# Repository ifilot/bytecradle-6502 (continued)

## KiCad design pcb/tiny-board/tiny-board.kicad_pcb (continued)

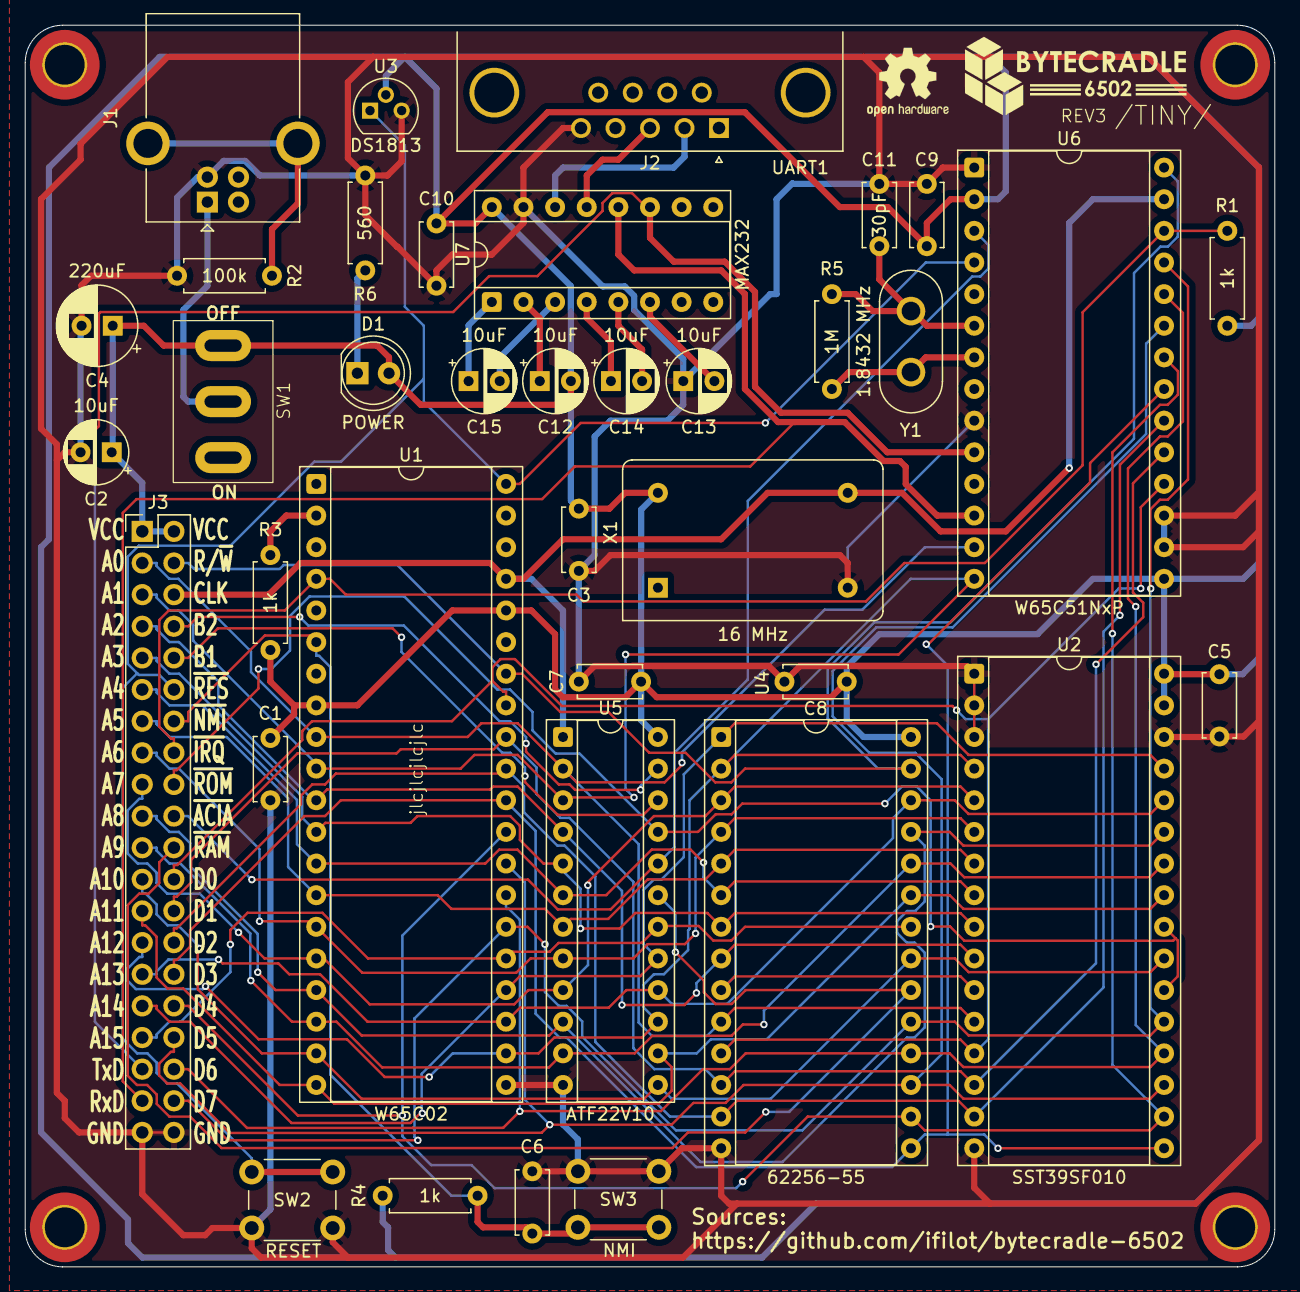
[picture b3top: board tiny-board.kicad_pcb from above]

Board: 2 copper layers, 100.3 x 99.7 mm, 42 parts (0 on the bottom side), 52 nets.

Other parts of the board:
G002: OSHW-Logo2_7.3x6mm_SilkScreen

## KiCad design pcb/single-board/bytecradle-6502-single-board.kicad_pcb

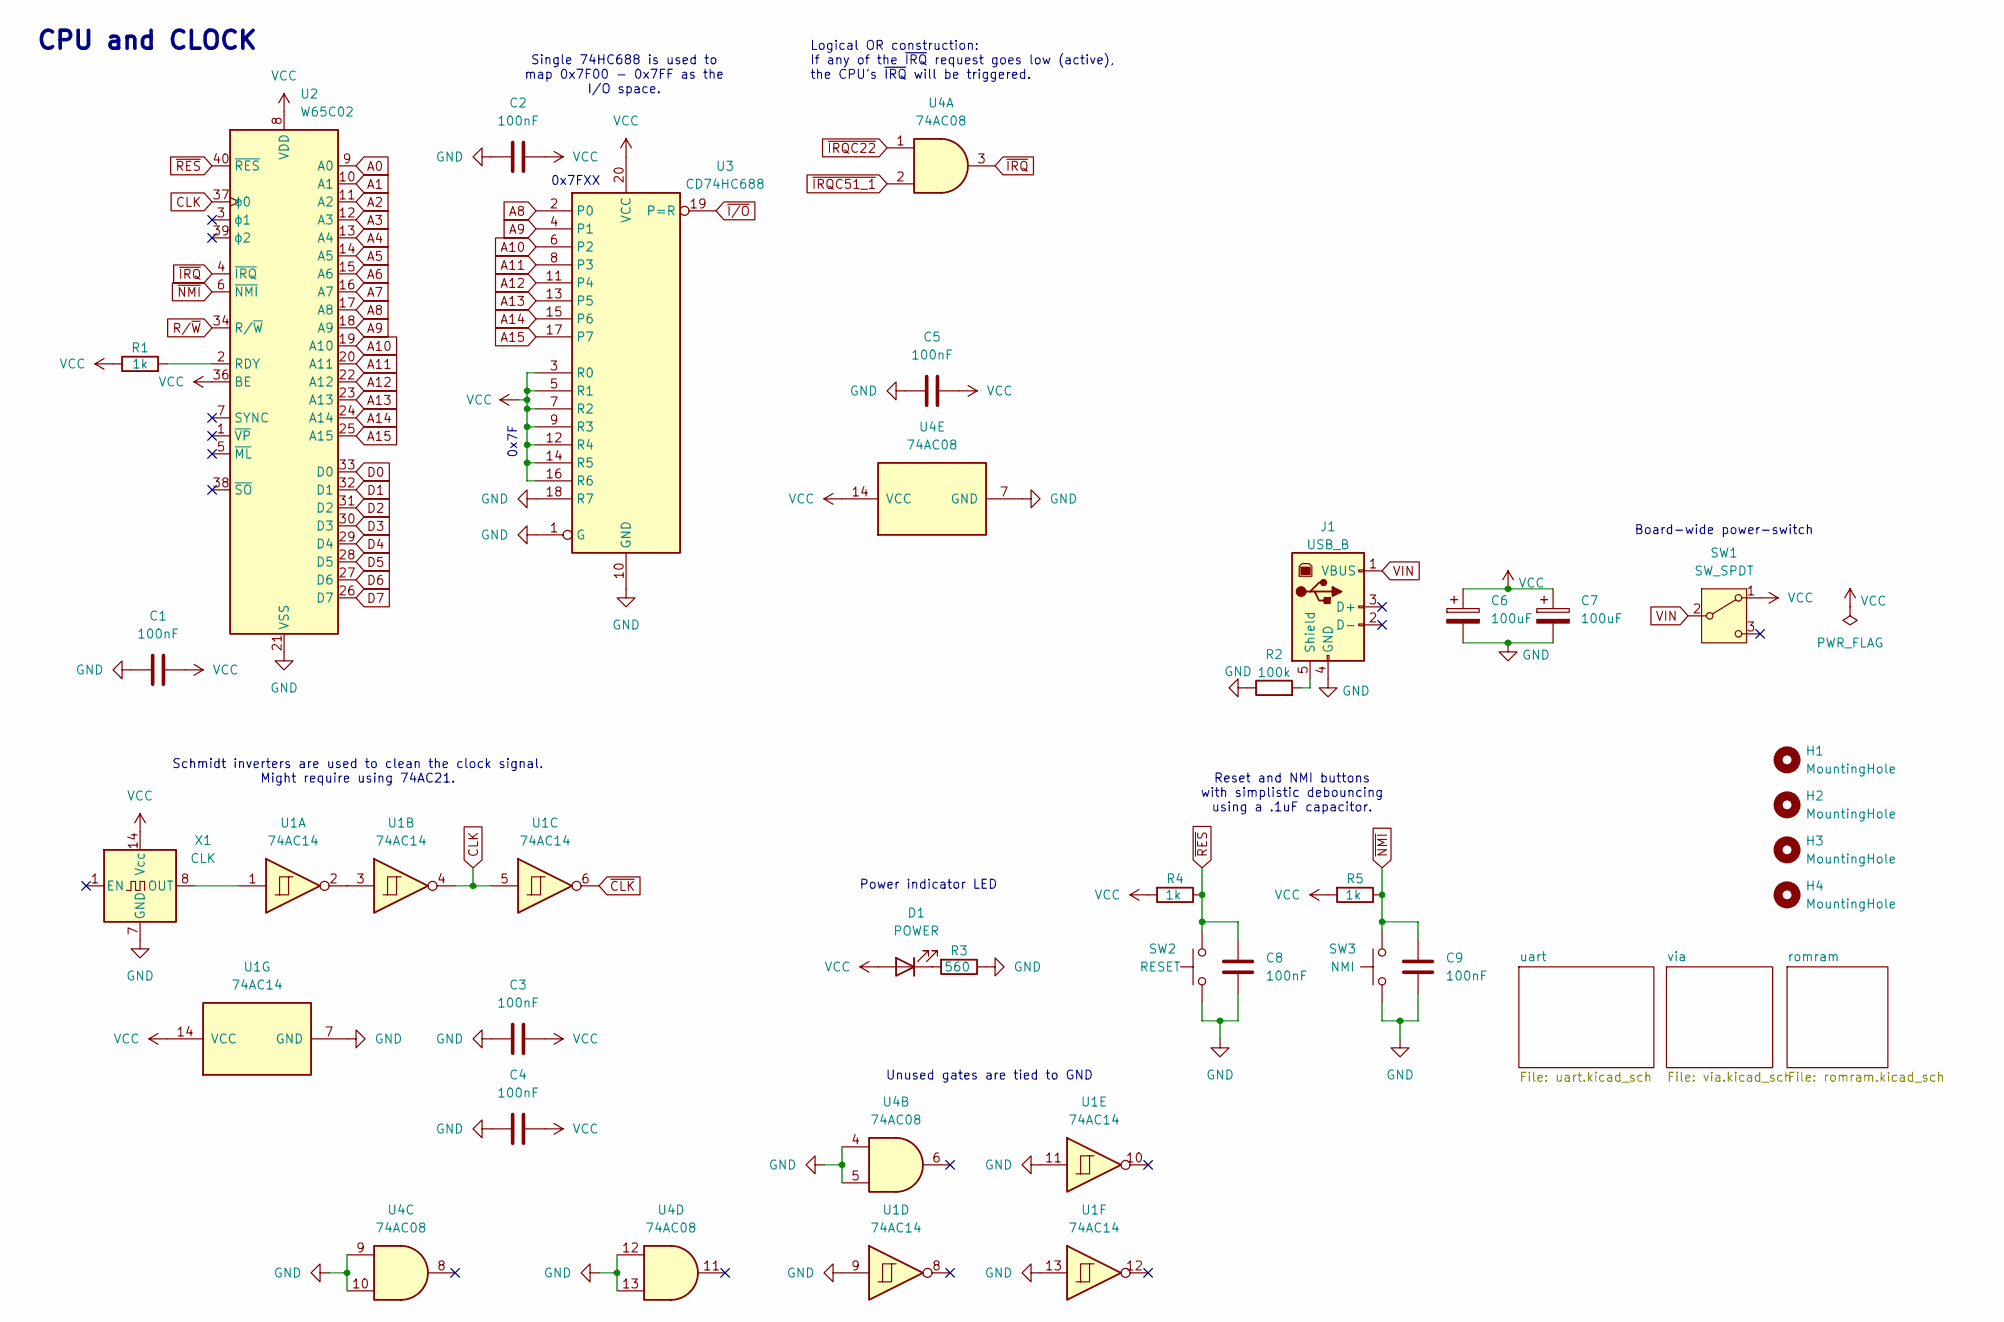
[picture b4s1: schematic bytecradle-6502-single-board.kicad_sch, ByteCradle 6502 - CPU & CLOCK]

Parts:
C1, C2, C3, C4, C5, C8, C9: 100nF; C_Disc_D5.0mm_W2.5mm_P5.00mm
C6, C7: 100uF; CP_Radial_D6.3mm_P2.50mm
D1: POWER; LED_D5.0mm
H1, H2, H3, H4: MountingHole; MountingHole_3.2mm_M3_DIN965_Pad_TopOnly
J1: USB_B; USB_B_OST_USB-B1HSxx_Horizontal
R1, R4, R5: 1k; R_Axial_DIN0207_L6.3mm_D2.5mm_P7.62mm_Horizontal
R2: 100k; R_Axial_DIN0207_L6.3mm_D2.5mm_P7.62mm_Horizontal
R3: 560; R_Axial_DIN0207_L6.3mm_D2.5mm_P7.62mm_Horizontal
SW1: SW_SPDT; power_switch
SW2: RESET; SW_PUSH_6mm
SW3: NMI; SW_PUSH_6mm
U1: 74AC14; DIP-14_W7.62mm_Socket
U2: W65C02; DIP-40_W15.24mm_Socket
U3: CD74HC688; DIP-20_W7.62mm_Socket
U4: 74AC08; DIP-14_W7.62mm_Socket
X1: CLK; Oscillator_DIP-14

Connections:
A0: U2.9 (A0); also elsewhere on the board
A1: U2.10 (A1); also elsewhere on the board
A2: U2.11 (A2); also elsewhere on the board
A3: U2.12 (A3); also elsewhere on the board
A4: U2.13 (A4); also elsewhere on the board
A5: U2.14 (A5); also elsewhere on the board
A6: U2.15 (A6); also elsewhere on the board
A7: U2.16 (A7); also elsewhere on the board
A8: U2.17 (A8), U3.2 (P0); also elsewhere on the board
A9: U2.18 (A9), U3.4 (P1); also elsewhere on the board
A10: U2.19 (A10), U3.6 (P2); also elsewhere on the board
A11: U2.20 (A11), U3.8 (P3); also elsewhere on the board
A12: U2.22 (A12), U3.11 (P4); also elsewhere on the board
A13: U2.23 (A13), U3.13 (P5); also elsewhere on the board
A14: U2.24 (A14), U3.15 (P6); also elsewhere on the board
A15: U2.25 (A15), U3.17 (P7); also elsewhere on the board
CLK: U1.4, U1.5, U2.37 (ϕ0); also elsewhere on the board
D0: U2.33 (D0); also elsewhere on the board
D1: U2.32 (D1); also elsewhere on the board
D2: U2.31 (D2); also elsewhere on the board
D3: U2.30 (D3); also elsewhere on the board
D4: U2.29 (D4); also elsewhere on the board
D5: U2.28 (D5); also elsewhere on the board
D6: U2.27 (D6); also elsewhere on the board
D7: U2.26 (D7); also elsewhere on the board
GND: C1.2, C2.2, C3.2, C4.2, C5.2, C6.2, C7.2, C8.2, C9.2, J1.4 (GND), R2.1, R3.1, SW2.1, SW3.1, U1.7 (GND), U1.9, U1.11, U1.13, U2.21 (VSS), U3.1 (G), U3.10 (GND), U3.18 (R7), U4.4, U4.5, U4.7 (GND), U4.9, U4.10, U4.12, U4.13, X1.7 (GND); also elsewhere on the board
unnamed: D1.1 (K), R3.2
unnamed: J1.5 (Shield), R2.2
unnamed: U1.2, U1.3
unnamed: R1.2, U2.2 (RDY)
unnamed: U1.1, X1.8 (OUT)
R/~W: U2.34 (R/~W); also elsewhere on the board
VCC: C1.1, C2.1, C3.1, C4.1, C5.1, C6.1, C7.1, D1.2 (A), R1.1, R4.2, R5.2, SW1.1 (A), U1.14 (VCC), U2.8 (VDD), U2.36 (BE), U3.3 (R0), U3.5 (R1), U3.7 (R2), U3.9 (R3), U3.12 (R4), U3.14 (R5), U3.16 (R6), U3.20 (VCC), U4.14 (VCC), X1.14 (Vcc); also elsewhere on the board
VIN: J1.1 (VBUS), SW1.2 (B)
~CLK: U1.6
~IRQC22: U4.1; also elsewhere on the board
~IRQC51_1: U4.2; also elsewhere on the board
~IRQ: U2.4 (~IRQ), U4.3
~I/O: U3.19 (P=R); also elsewhere on the board
~NMI: C9.1, R5.1, SW3.2, U2.6 (~NMI); also elsewhere on the board
~RES: C8.1, R4.1, SW2.2, U2.40 (~RES); also elsewhere on the board

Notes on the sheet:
0x7F
Reset and NMI buttons with simplistic debouncing using a .1uF capacitor.
Schmidt inverters are used to clean the clock signal. Might require using 74AC21.
0x7FXX
Power indicator LED
Single 74HC688 is used to map 0x7F00 - 0x7FF as the I/O space.
CPU and CLOCK
Board-wide power-switch
Logical OR construction: If any of the ~{IRQ} request goes low (active), the CPU's ~{IRQ} will be triggered.
Unused gates are tied to GND

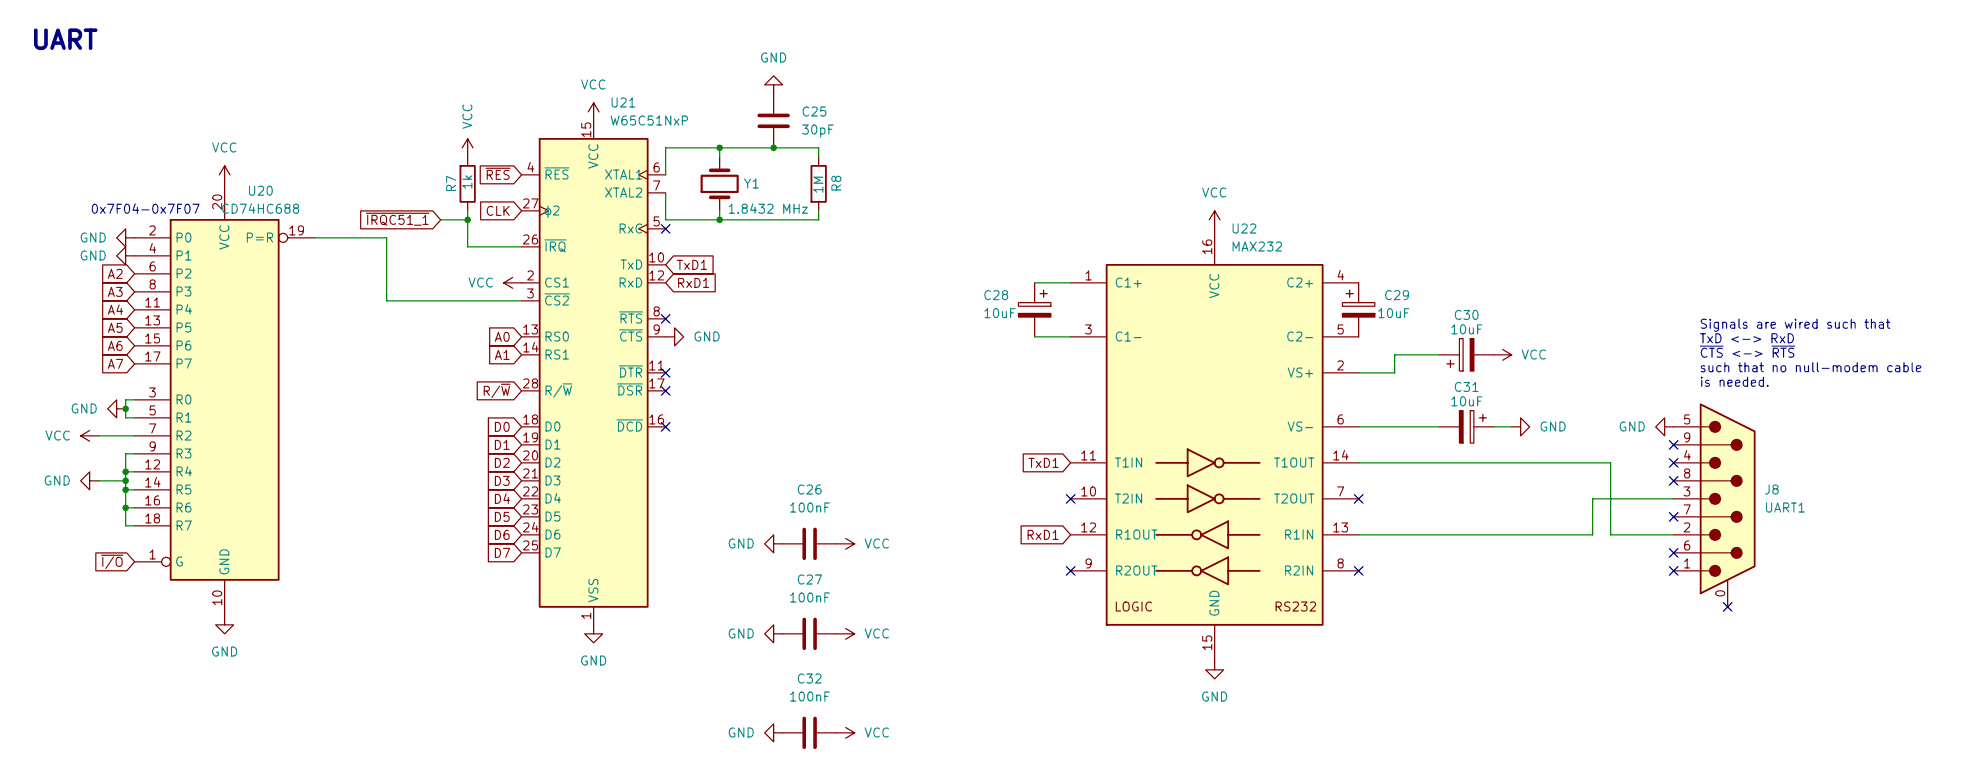
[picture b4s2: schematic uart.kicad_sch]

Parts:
C25: 30pF; C_Disc_D5.0mm_W2.5mm_P5.00mm
C26, C27, C32: 100nF; C_Disc_D5.0mm_W2.5mm_P5.00mm
C28, C29, C30, C31: 10uF; CP_Radial_D5.0mm_P2.50mm
J8: UART1; DSUB-9_Pins_Horizontal_P2.77x2.84mm_EdgePinOffset4.94mm_Hou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
R7: 1k; R_Axial_DIN0207_L6.3mm_D2.5mm_P7.62mm_Horizontal
R8: 1M; R_Axial_DIN0207_L6.3mm_D2.5mm_P7.62mm_Horizontal
U20: CD74HC688; DIP-20_W7.62mm_Socket
U21: W65C51NxP; DIP-28_W15.24mm_Socket
U22: MAX232; DIP-16_W7.62mm_Socket
Y1: 1.8432 MHz; Crystal_HC50_Vertical

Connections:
A0: U21.13 (RS0); also elsewhere on the board
A1: U21.14 (RS1); also elsewhere on the board
A2: U20.6 (P2); also elsewhere on the board
A3: U20.8 (P3); also elsewhere on the board
A4: U20.11 (P4); also elsewhere on the board
A5: U20.13 (P5); also elsewhere on the board
A6: U20.15 (P6); also elsewhere on the board
A7: U20.17 (P7); also elsewhere on the board
CLK: U21.27 (ϕ2); also elsewhere on the board
D0: U21.18 (D0); also elsewhere on the board
D1: U21.19 (D1); also elsewhere on the board
D2: U21.20 (D2); also elsewhere on the board
D3: U21.21 (D3); also elsewhere on the board
D4: U21.22 (D4); also elsewhere on the board
D5: U21.23 (D5); also elsewhere on the board
D6: U21.24 (D6); also elsewhere on the board
D7: U21.25 (D7); also elsewhere on the board
GND: C25.1, C26.2, C27.2, C31.1, C32.2, J8.5, U20.2 (P0), U20.3 (R0), U20.4 (P1), U20.5 (R1), U20.9 (R3), U20.10 (GND), U20.12 (R4), U20.14 (R5), U20.16 (R6), U20.18 (R7), U21.1 (VSS), U21.9 (~CTS), U22.15 (GND); also elsewhere on the board
unnamed: U20.19 (P=R), U21.3 (~CS2)
unnamed: C25.2, R8.1, U21.6 (XTAL1), Y1.2
unnamed: R8.2, U21.7 (XTAL2), Y1.1
unnamed: C28.1, U22.1 (C1+)
unnamed: C28.2, U22.3 (C1-)
unnamed: C29.1, U22.4 (C2+)
unnamed: C29.2, U22.5 (C2-)
unnamed: J8.3, U22.13 (R1IN)
unnamed: J8.2, U22.14 (T1OUT)
unnamed: C30.1, U22.2 (VS+)
unnamed: C31.2, U22.6 (VS-)
RxD1: U21.12 (RxD), U22.12 (R1OUT)
R/~W: U21.28 (R/~W); also elsewhere on the board
TxD1: U21.10 (TxD), U22.11 (T1IN)
VCC: C26.1, C27.1, C30.2, C32.1, R7.2, U20.7 (R2), U20.20 (VCC), U21.2 (CS1), U21.15 (VCC), U22.16 (VCC); also elsewhere on the board
~IRQC51_1: R7.1, U21.26 (~IRQ); also elsewhere on the board
~I/O: U20.1 (G); also elsewhere on the board
~RES: U21.4 (~RES); also elsewhere on the board

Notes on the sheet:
UART
0x7F04-0x7F07
Signals are wired such that TxD <-> RxD ~{CTS} <-> ~{RTS} such that no null-modem cable is needed.

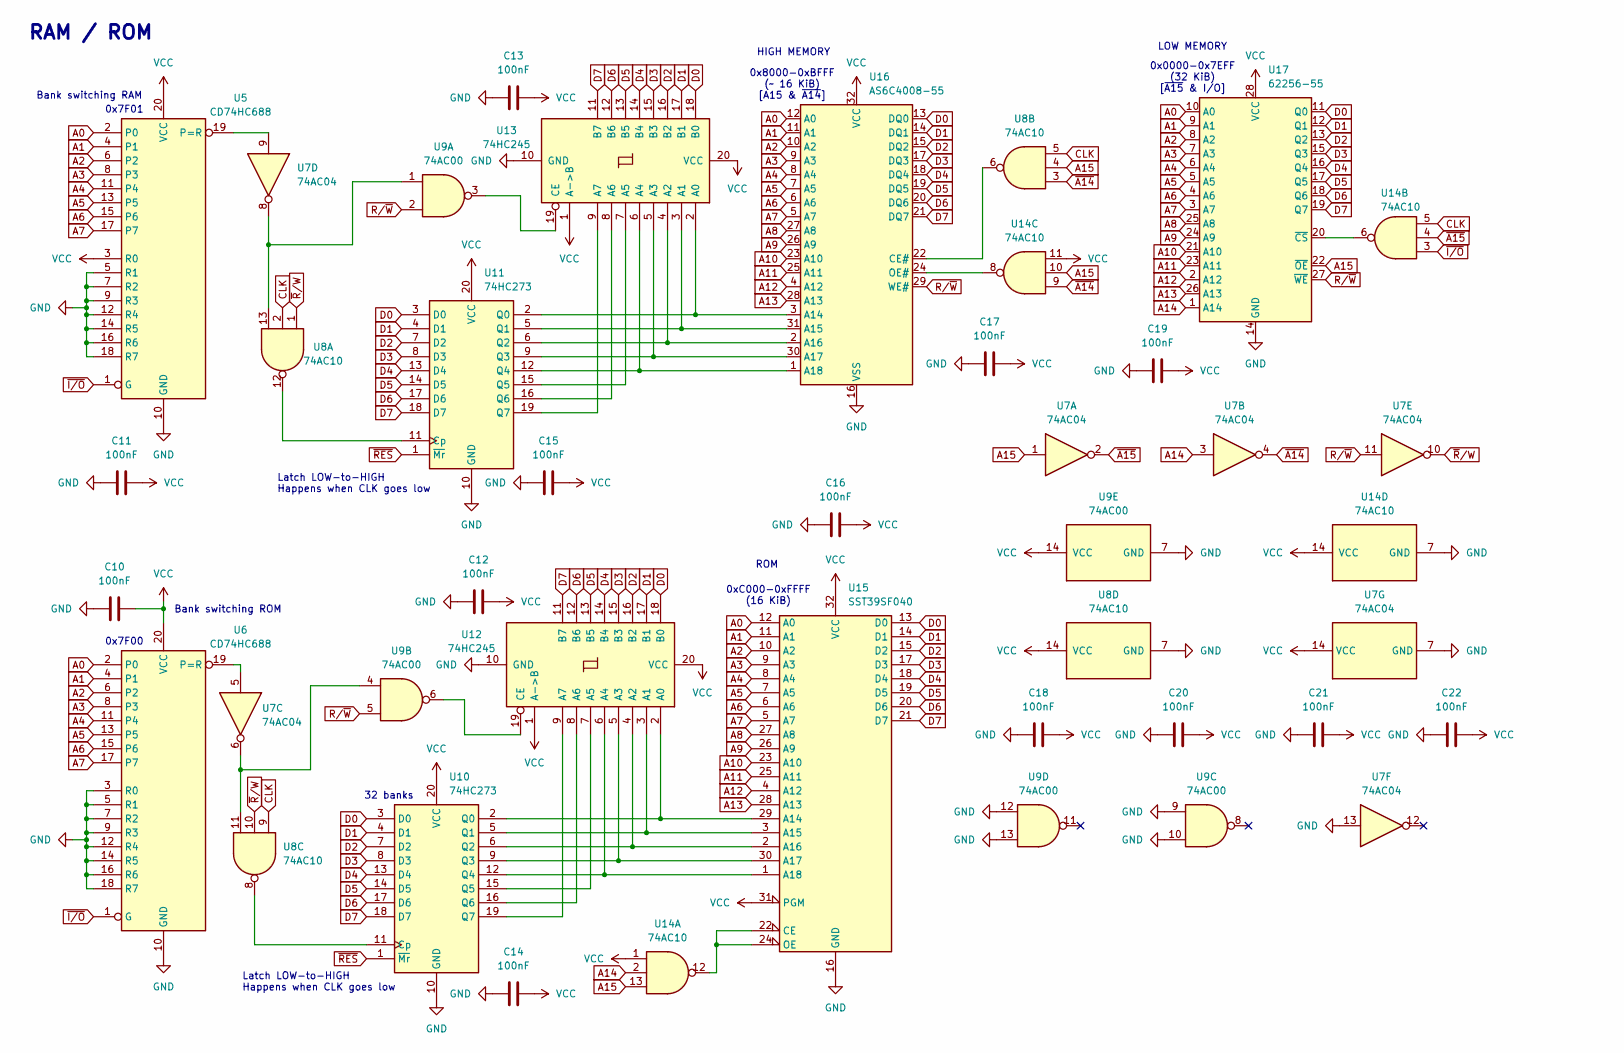
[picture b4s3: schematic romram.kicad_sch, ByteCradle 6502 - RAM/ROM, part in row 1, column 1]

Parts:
C10, C11, C12, C13, C14, C15, C16, C17, C18, C19, C20, C21, C22: 100nF; C_Disc_D5.0mm_W2.5mm_P5.00mm
U5, U6: CD74HC688; DIP-20_W7.62mm_Socket
U7: 74AC04; DIP-14_W7.62mm_Socket
U8, U14: 74AC10; DIP-14_W7.62mm_Socket
U9: 74AC00; DIP-14_W7.62mm_Socket
U10, U11: 74HC273; DIP-20_W7.62mm_Socket
U12, U13: 74HC245; DIP-20_W7.62mm_Socket
U15: SST39SF040; DIP-32_W15.24mm_Socket
U16: AS6C4008-55; DIP-32_W15.24mm_Socket
U17: 62256-55; DIP-28_W15.24mm_Socket

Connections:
A0: U5.2 (P0), U6.2 (P0), U15.12 (A0), U16.12 (A0), U17.10 (A0); also elsewhere on the board
A1: U5.4 (P1), U6.4 (P1), U15.11 (A1), U16.11 (A1), U17.9 (A1); also elsewhere on the board
A2: U5.6 (P2), U6.6 (P2), U15.10 (A2), U16.10 (A2), U17.8 (A2); also elsewhere on the board
A3: U5.8 (P3), U6.8 (P3), U15.9 (A3), U16.9 (A3), U17.7 (A3); also elsewhere on the board
A4: U5.11 (P4), U6.11 (P4), U15.8 (A4), U16.8 (A4), U17.6 (A4); also elsewhere on the board
A5: U5.13 (P5), U6.13 (P5), U15.7 (A5), U16.7 (A5), U17.5 (A5); also elsewhere on the board
A6: U5.15 (P6), U6.15 (P6), U15.6 (A6), U16.6 (A6), U17.4 (A6); also elsewhere on the board
A7: U5.17 (P7), U6.17 (P7), U15.5 (A7), U16.5 (A7), U17.3 (A7); also elsewhere on the board
A8: U15.27 (A8), U16.27 (A8), U17.25 (A8); also elsewhere on the board
A9: U15.26 (A9), U16.26 (A9), U17.24 (A9); also elsewhere on the board
A10: U15.23 (A10), U16.23 (A10), U17.21 (A10); also elsewhere on the board
A11: U15.25 (A11), U16.25 (A11), U17.23 (A11); also elsewhere on the board
A12: U15.4 (A12), U16.4 (A12), U17.2 (A12); also elsewhere on the board
A13: U15.28 (A13), U16.28 (A13), U17.26 (A13); also elsewhere on the board
A14: U7.3, U14.2, U17.1 (A14); also elsewhere on the board
A15: U7.1, U8.4, U14.10, U14.13, U17.22 (~OE); also elsewhere on the board
CLK: U8.2, U8.5, U8.9, U14.5; also elsewhere on the board
D0: U10.3 (D0), U11.3 (D0), U12.18 (B0), U13.18 (B0), U15.13 (D0), U16.13 (DQ0), U17.11 (Q0); also elsewhere on the board
D1: U10.4 (D1), U11.4 (D1), U12.17 (B1), U13.17 (B1), U15.14 (D1), U16.14 (DQ1), U17.12 (Q1); also elsewhere on the board
D2: U10.7 (D2), U11.7 (D2), U12.16 (B2), U13.16 (B2), U15.15 (D2), U16.15 (DQ2), U17.13 (Q2); also elsewhere on the board
D3: U10.8 (D3), U11.8 (D3), U12.15 (B3), U13.15 (B3), U15.17 (D3), U16.17 (DQ3), U17.15 (Q3); also elsewhere on the board
D4: U10.13 (D4), U11.13 (D4), U12.14 (B4), U13.14 (B4), U15.18 (D4), U16.18 (DQ4), U17.16 (Q4); also elsewhere on the board
D5: U10.14 (D5), U11.14 (D5), U12.13 (B5), U13.13 (B5), U15.19 (D5), U16.19 (DQ5), U17.17 (Q5); also elsewhere on the board
D6: U10.17 (D6), U11.17 (D6), U12.12 (B6), U13.12 (B6), U15.20 (D6), U16.20 (DQ6), U17.18 (Q6); also elsewhere on the board
D7: U10.18 (D7), U11.18 (D7), U12.11 (B7), U13.11 (B7), U15.21 (D7), U16.21 (DQ7), U17.19 (Q7); also elsewhere on the board
GND: C10.2, C11.2, C12.2, C13.2, C14.2, C15.2, C16.2, C17.2, C18.2, C19.2, C20.2, C21.2, C22.2, U5.5 (R1), U5.7 (R2), U5.9 (R3), U5.10 (GND), U5.12 (R4), U5.14 (R5), U5.16 (R6), U5.18 (R7), U6.3 (R0), U6.5 (R1), U6.7 (R2), U6.9 (R3), U6.10 (GND), U6.12 (R4), U6.14 (R5), U6.16 (R6), U6.18 (R7), U7.7 (GND), U7.13, U8.7 (GND), U9.7 (GND), U9.9, U9.10, U9.12, U9.13, U10.10 (GND), U11.10 (GND), U12.10 (GND), U13.10 (GND), U14.7 (GND), U15.16 (GND), U16.16 (VSS), U17.14 (GND); also elsewhere on the board
unnamed: U5.19 (P=R), U7.9
unnamed: U6.19 (P=R), U7.5
unnamed: U7.6, U8.11, U9.4
unnamed: U7.8, U8.13, U9.1
unnamed: U8.8, U10.11 (Cp)
unnamed: U10.2 (Q0), U12.2 (A0), U15.29 (A14)
unnamed: U10.5 (Q1), U12.3 (A1), U15.3 (A15)
unnamed: U10.6 (Q2), U12.4 (A2), U15.2 (A16)
unnamed: U10.9 (Q3), U12.5 (A3), U15.30 (A17)
unnamed: U10.12 (Q4), U12.6 (A4), U15.1 (A18)
unnamed: U10.15 (Q5), U12.7 (A5)
unnamed: U10.16 (Q6), U12.8 (A6)
unnamed: U10.19 (Q7), U12.9 (A7)
unnamed: U8.12, U11.11 (Cp)
unnamed: U11.2 (Q0), U13.2 (A0), U16.3 (A14)
unnamed: U11.5 (Q1), U13.3 (A1), U16.31 (A15)
unnamed: U11.6 (Q2), U13.4 (A2), U16.2 (A16)
unnamed: U11.9 (Q3), U13.5 (A3), U16.30 (A17)
unnamed: U11.12 (Q4), U13.6 (A4), U16.1 (A18)
unnamed: U11.15 (Q5), U13.7 (A5)
unnamed: U11.16 (Q6), U13.8 (A6)
unnamed: U11.19 (Q7), U13.9 (A7)
unnamed: U9.6, U12.19 (CE)
unnamed: U9.3, U13.19 (CE)
unnamed: U14.12, U15.22 (CE), U15.24 (OE)
unnamed: U8.6, U16.22 (CE#)
unnamed: U14.8, U16.24 (OE#)
unnamed: U14.6, U17.20 (~CS)
R/~W: U7.11, U9.2, U9.5, U16.29 (WE#), U17.27 (~WE); also elsewhere on the board
VCC: C10.1, C11.1, C12.1, C13.1, C14.1, C15.1, C16.1, C17.1, C18.1, C19.1, C20.1, C21.1, C22.1, U5.3 (R0), U5.20 (VCC), U6.20 (VCC), U7.14 (VCC), U8.14 (VCC), U9.14 (VCC), U10.20 (VCC), U11.20 (VCC), U12.1 (A->B), U12.20 (VCC), U13.1 (A->B), U13.20 (VCC), U14.1, U14.11, U14.14 (VCC), U15.31 (PGM), U15.32 (VCC), U16.32 (VCC), U17.28 (VCC); also elsewhere on the board
~A14: U7.4, U8.3, U14.9
~A15: U7.2, U14.4
~I/O: U5.1 (G), U6.1 (G), U14.3; also elsewhere on the board
~RES: U10.1 (~Mr), U11.1 (~Mr); also elsewhere on the board
~R/W: U7.10, U8.1, U8.10

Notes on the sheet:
0x8000-0xBFFF (~ 16 KiB) [A15 & ~{A14}]
0x7F00
0x7F01
Bank switching ROM
LOW MEMORY
32 banks
Latch LOW-to-HIGH Happens when CLK goes low
ROM
RAM / ROM
0x0000-0x7EFF (32 KiB) [~{A15} & I/O]
0xC000-0xFFFF (16 KiB)
Bank switching RAM
HIGH MEMORY

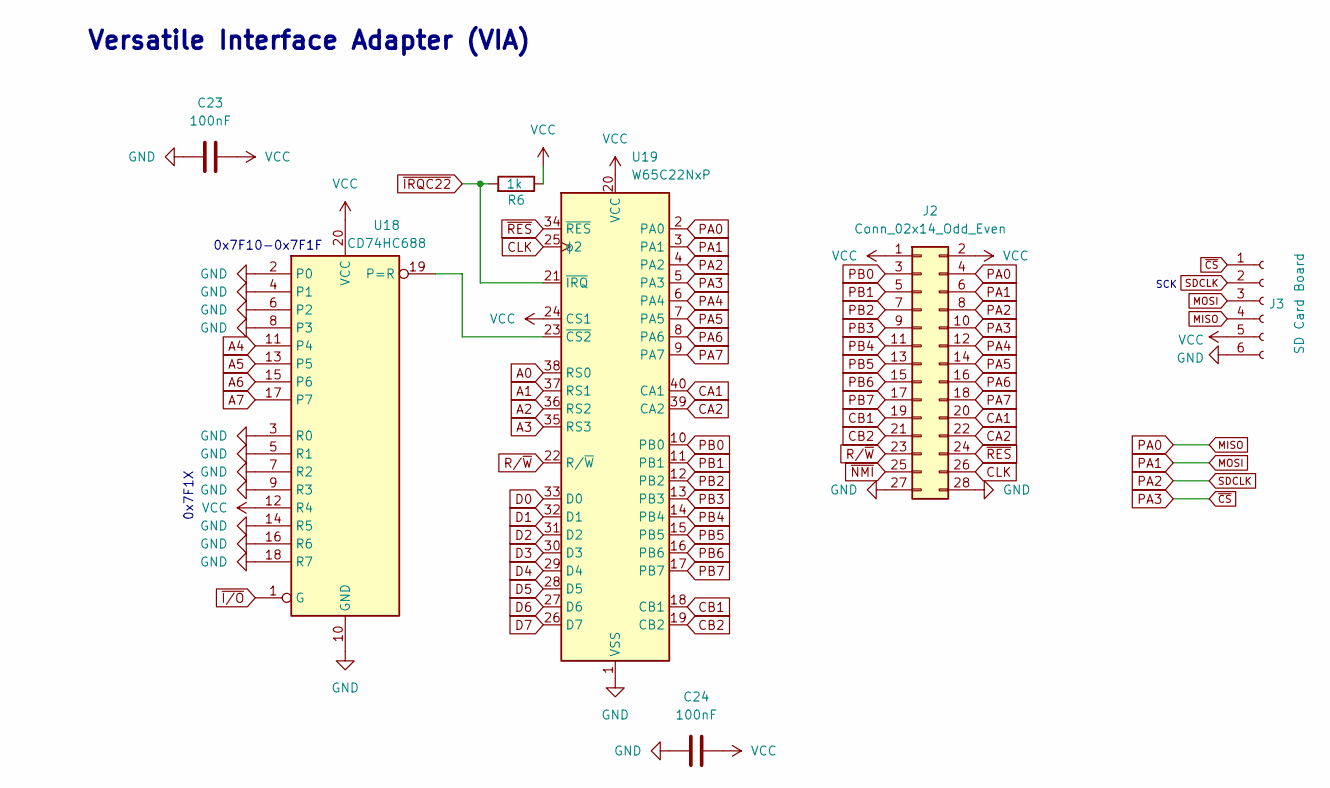
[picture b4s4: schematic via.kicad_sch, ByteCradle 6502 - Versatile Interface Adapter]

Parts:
C23, C24: 100nF; C_Disc_D5.0mm_W2.5mm_P5.00mm
J2: Conn_02x14_Odd_Even; PinHeader_2x14_P2.54mm_Vertical
J3: SD Card Board; sdcard-socket
R6: 1k; R_Axial_DIN0207_L6.3mm_D2.5mm_P7.62mm_Horizontal
U18: CD74HC688; DIP-20_W7.62mm_Socket
U19: W65C22NxP; DIP-40_W15.24mm_Socket

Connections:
A0: U19.38 (RS0); also elsewhere on the board
A1: U19.37 (RS1); also elsewhere on the board
A2: U19.36 (RS2); also elsewhere on the board
A3: U19.35 (RS3); also elsewhere on the board
A4: U18.11 (P4); also elsewhere on the board
A5: U18.13 (P5); also elsewhere on the board
A6: U18.15 (P6); also elsewhere on the board
A7: U18.17 (P7); also elsewhere on the board
CA1: J2.20, U19.40 (CA1)
CA2: J2.22, U19.39 (CA2)
CB1: J2.19, U19.18 (CB1)
CB2: J2.21, U19.19 (CB2)
CLK: J2.26, U19.25 (ϕ2); also elsewhere on the board
D0: U19.33 (D0); also elsewhere on the board
D1: U19.32 (D1); also elsewhere on the board
D2: U19.31 (D2); also elsewhere on the board
D3: U19.30 (D3); also elsewhere on the board
D4: U19.29 (D4); also elsewhere on the board
D5: U19.28 (D5); also elsewhere on the board
D6: U19.27 (D6); also elsewhere on the board
D7: U19.26 (D7); also elsewhere on the board
GND: C23.2, C24.2, J2.27, J2.28, J3.6, U18.2 (P0), U18.3 (R0), U18.4 (P1), U18.5 (R1), U18.6 (P2), U18.7 (R2), U18.8 (P3), U18.9 (R3), U18.10 (GND), U18.14 (R5), U18.16 (R6), U18.18 (R7), U19.1 (VSS); also elsewhere on the board
MISO: J2.4, J3.4, U19.2 (PA0)
MOSI: J2.6, J3.3, U19.3 (PA1)
unnamed: U18.19 (P=R), U19.23 (~CS2)
PA2: J2.8, J3.2, U19.4 (PA2)
PA3: J2.10, J3.1, U19.5 (PA3)
PA4: J2.12, U19.6 (PA4)
PA5: J2.14, U19.7 (PA5)
PA6: J2.16, U19.8 (PA6)
PA7: J2.18, U19.9 (PA7)
PB0: J2.3, U19.10 (PB0)
PB1: J2.5, U19.11 (PB1)
PB2: J2.7, U19.12 (PB2)
PB3: J2.9, U19.13 (PB3)
PB4: J2.11, U19.14 (PB4)
PB5: J2.13, U19.15 (PB5)
PB6: J2.15, U19.16 (PB6)
PB7: J2.17, U19.17 (PB7)
R/~W: J2.23, U19.22 (R/~W); also elsewhere on the board
VCC: C23.1, C24.1, J2.1, J2.2, J3.5, R6.1, U18.12 (R4), U18.20 (VCC), U19.20 (VCC), U19.24 (CS1); also elsewhere on the board
~IRQC22: R6.2, U19.21 (~IRQ); also elsewhere on the board
~I/O: U18.1 (G); also elsewhere on the board
~NMI: J2.25; also elsewhere on the board
~RES: J2.24, U19.34 (~RES); also elsewhere on the board

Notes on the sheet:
0x7F10-0x7F1F
SCK
Versatile Interface Adapter (VIA)
0x7F1X

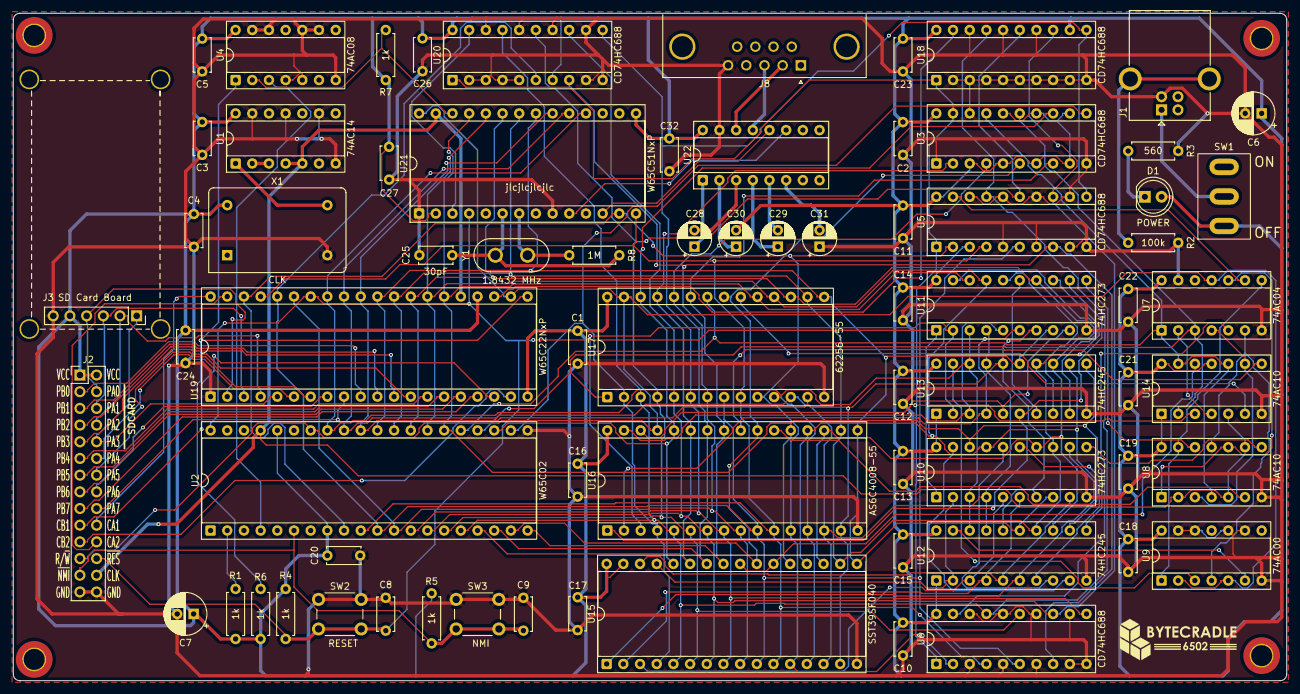
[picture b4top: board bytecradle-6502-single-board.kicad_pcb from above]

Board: 2 copper layers, 193.9 x 101.6 mm, 76 parts (0 on the bottom side), 105 nets.

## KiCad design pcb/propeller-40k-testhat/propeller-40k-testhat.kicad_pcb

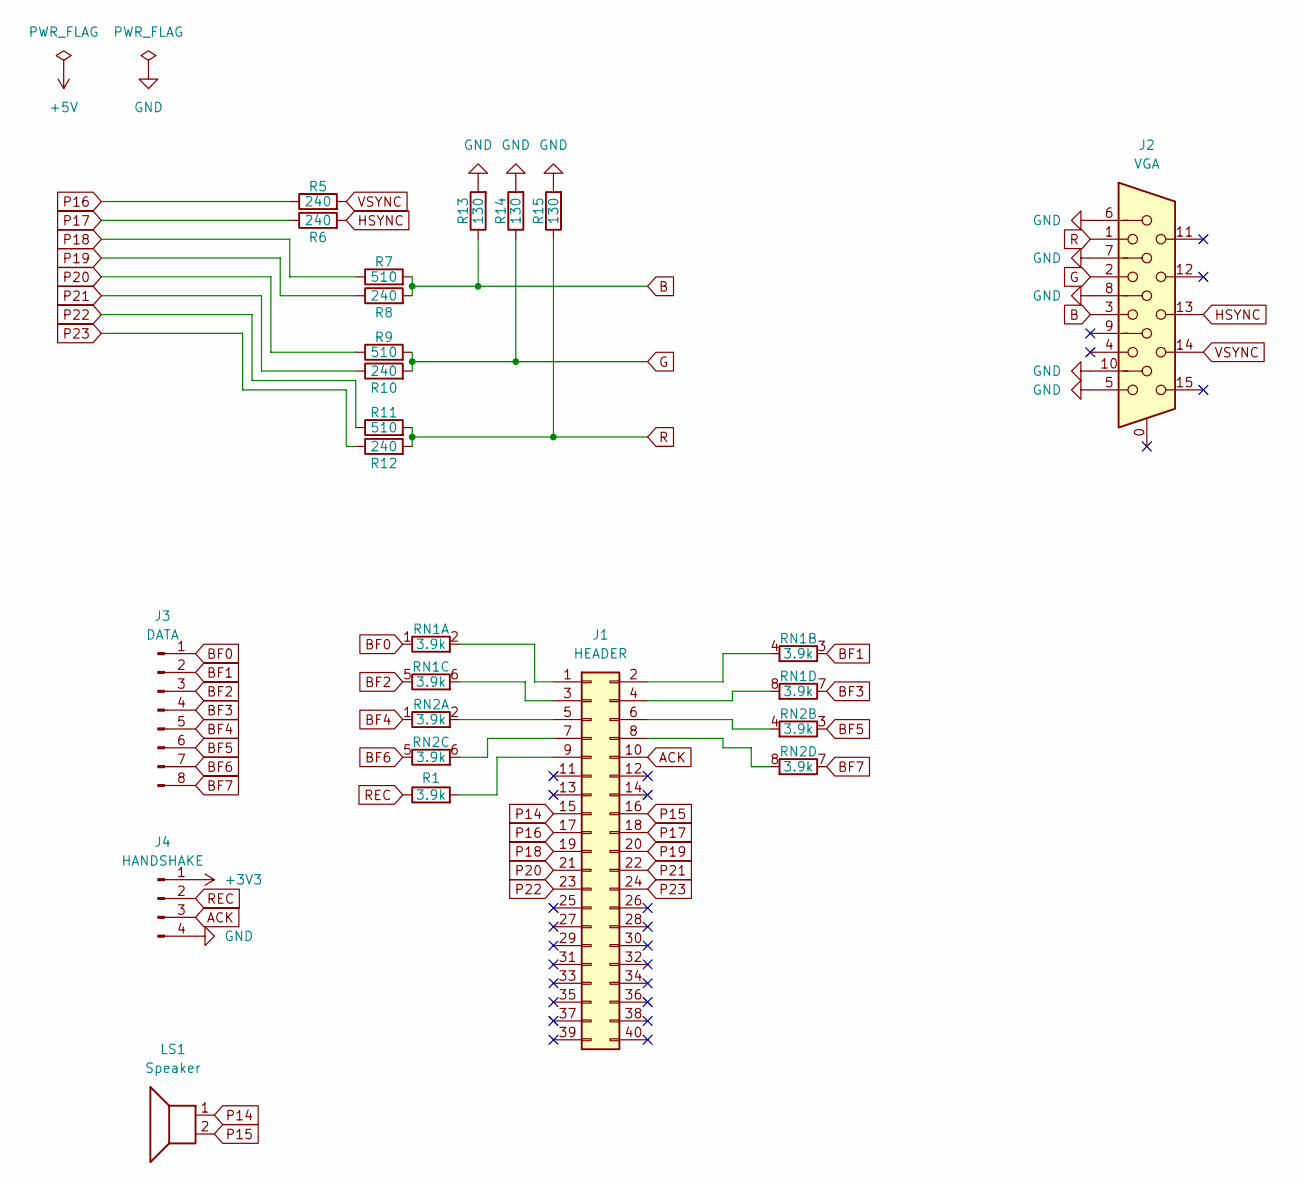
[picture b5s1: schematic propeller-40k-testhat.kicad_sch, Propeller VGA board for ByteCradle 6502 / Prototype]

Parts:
J1: HEADER; PinHeader_2x20_P2.54mm_Vertical
J2: VGA; 618015330923
J3: DATA; PinSocket_1x08_P2.54mm_Vertical
J4: HANDSHAKE; PinSocket_1x04_P2.54mm_Vertical
LS1: Speaker; MagneticBuzzer_ProSignal_ABI-009-RC
R1: 3.9k; R_Axial_DIN0207_L6.3mm_D2.5mm_P7.62mm_Horizontal
R5, R6, R8, R10, R12: 240; R_Axial_DIN0207_L6.3mm_D2.5mm_P7.62mm_Horizontal
R7, R9, R11: 510; R_Axial_DIN0207_L6.3mm_D2.5mm_P7.62mm_Horizontal
R13, R14, R15: 130; R_Axial_DIN0207_L6.3mm_D2.5mm_P7.62mm_Horizontal
RN1, RN2: 3.9k; R_Array_SIP8

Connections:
+3V3: J4.1
ACK: J1.10, J4.3
B: J2.3, R7.2, R8.2, R13.1
BF0: J3.1, RN1.1 (R1.1)
BF1: J3.2, RN1.3 (R2.1)
BF2: J3.3, RN1.5 (R3.1)
BF3: J3.4, RN1.7 (R4.1)
BF4: J3.5, RN2.1 (R1.1)
BF5: J3.6, RN2.3 (R2.1)
BF6: J3.7, RN2.5 (R3.1)
BF7: J3.8, RN2.7 (R4.1)
G: J2.2, R9.2, R10.2, R14.1
GND: J2.5, J2.6, J2.7, J2.8, J2.10, J4.4, R13.2, R14.2, R15.2
HSYNC: J2.13, R6.2
unnamed: J1.1, RN1.2 (R1.2)
unnamed: J1.2, RN1.4 (R2.2)
unnamed: J1.3, RN1.6 (R3.2)
unnamed: J1.4, RN1.8 (R4.2)
unnamed: J1.5, RN2.2 (R1.2)
unnamed: J1.6, RN2.4 (R2.2)
unnamed: J1.7, RN2.6 (R3.2)
unnamed: J1.8, RN2.8 (R4.2)
unnamed: J1.9, R1.2
P14: J1.15, LS1.1
P15: J1.16, LS1.2
P16: J1.17, R5.1
P17: J1.18, R6.1
P18: J1.19, R7.1
P19: J1.20, R8.1
P20: J1.21, R9.1
P21: J1.22, R10.1
P22: J1.23, R11.1
P23: J1.24, R12.1
R: J2.1, R11.2, R12.2, R15.1
REC: J4.2, R1.1
VSYNC: J2.14, R5.2

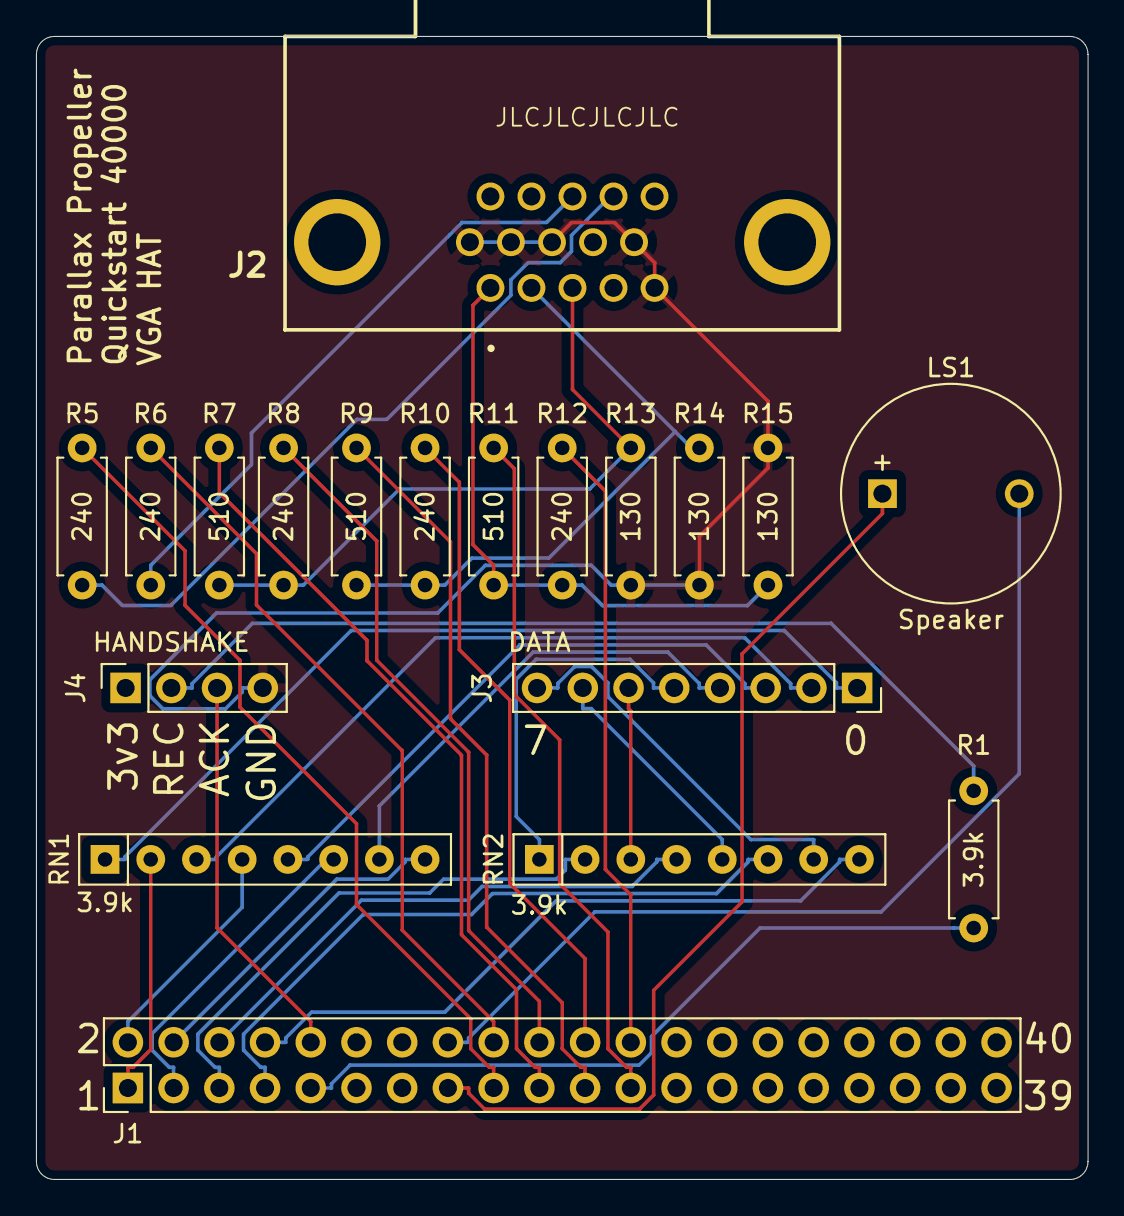
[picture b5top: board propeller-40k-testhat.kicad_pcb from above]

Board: 2 copper layers, 58.4 x 63.5 mm, 19 parts (0 on the bottom side), 35 nets.
